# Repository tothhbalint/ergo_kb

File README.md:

## Bevezetés

##### Az ergonomikus billentyűzetek világában sok „normál” billentyűzetek ismeretében

##### furcsának tűnő megoldás van. Általában egy billentyűzeten a gombok nem egy

##### oszlopban, hanem egy kis eltolással találhatóak meg, viszont ha a billentyűket egymás

##### alá helyezzük sokkal rövidebb úton érhetőek el a gombok, ezzel csökken az újnak a

##### fáradása. Hasonlóan érdekes megoldás a billentyűzet „kettőbe vágása”, ez is a

##### kényelmet segíti, a természetes csuklópozíció megtartásával. A feladat egy ilyen

##### billentyűzet megtervezése.

##### A tervezés első fázisa a kiosztás megtervezése. Minél kevesebb gombunk van annál

##### kényelmesebb lesz gépelni, viszont időbe telhet a kiosztás megszokása. Ebben a

##### projektben egy 36 gombos kiosztás lett megvalósítva, ami pont arra elég, hogy az angol

##### ABC betűi elférjenek rajta és a végén maradjon még 1-2 gomb. Jogosan felmerülhet,

##### hogy hogyan érjük el a többi karaktert, például a számokat? Erre rétegeket

##### használhatunk, amiket erre dedikált gombokkal érhetünk el, ezek lenyomásval a

##### billentyű másik karaktert jelez a cél eszközön, hasonlóan mintha egy módosító gombot

##### használnánk. Felmerülhet még az is, hogy a módosító gombokat hogyan érjük el.

##### Többféle megoldás létezik, a legegyszerűbb talán a gombok lenyomásának idejét

##### figyelni, és a hosszan lenyomott gombokat egy adott pozícióban módosító gombként

##### kezelni.

## PCB Tervezés

### Alkatrészek

##### Fontos meghatározni az alkatrészeket mielőtt nekiállunk a PCB tervezésének, hogy

##### konkrét footprinteket (az alkatrészek lábainak az elhelyezkedése a modellben) tudjunk

##### használni. A legfontosabb alkatrészek a billentyűkapcsolók, hogy regisztrálni tudjuk a

##### billentyűlenyomásokat, a mikrokontroller, ami feldolgozza az alkatrészekből érkező

##### jeleket. Kevésbé fontos alkatrészek az enkóderek és a kijelzők.

##### Mikrokontroller választásnál két fontos szempontom volt, legyen elég GPIO lába, legyen

##### Bluetooth támogatása. Végül az nrf5284 0 - re esett a választás, ami megfelelt ezeknek a

##### követelményeknek.

##### Billentyű kapcsolókat kétféle módon tudunk beszerelni az áramkörünkbe. Vagy direktbe

##### beforrasztjuk őket, vagy használunk úgynevezett „hotswap socket”eket, amik

##### egyszerűbbé teszik a billentyűk cseréit.

### Billentyűmátrix

##### Legtöbb esetben a mikrontrollerünknek kevesebb GPIOja van mint ahány gombja van a

##### billentyűzetünknek. Ez elsőre problémának tűnik, viszont van rá egy egyszerű megoldás.

##### A kapcsolókat egy mátrixba kötjük, az alábbi módon.

###### ábra 1 :Billentyűmátrix

##### Így a kontrollernek csak annyi lába kell hogy legyen, mint ahány oszlopunk és sorunk

##### van. Az oszlopokon küldünk egy aktív jelet, amit a sorokon kiolvasunk, vagy fordítva,

##### ezzel megállapíthatjuk, hogy melyik gomb lett lenyomva, mivel az zárja az áramkört.

##### Viszont így felmerül az úgynevezett „ghosting” problémája.

###### ábra 2 : Ghosting

##### Ahogy a képen is látszik a probléma, ha a képen látható három gomb le van nyomva,

##### akkor a kontroller a C3 gombot is regisztrálja, pedig az nincsen lenyomva.

##### Erre megoldás, ha diódákat rakunk az áramkörünkbe a gombok és a sorok köze, feltéve,

##### hogy az oszlopokon küldjuk a kimenete jelen és a sorokon várjuk a bemenetit. Ekkor a

##### kép szerinti C2 gombból nem folyik áram a C3 gombba, így a 3as bemeneten nem

##### figyelünk meg jelet.

### Billentyű elosztás

##### A billentyűk elosztásának megtervezéséhez egy Ergogen nevű projektet használtam, ami

##### egy magyar fejelsztő projektje. A program egy yaml fájlból generál KiCad fájlokat, de akár

##### házat is tervezhetünk vele a billentyűzetünknek. Tervezés közben megadhatjuk a

##### gombok pozícióját, egymáshoz relatívan, a perifériák elhelyezkedését és ami a

##### legfontosabb megtudjuk adni az oszlopokhoz rendelt lábakat a mikrokontrolleren.

###### ábra 3 : Ergogen kimenet

### PCB tervezés

##### Az ergogenben elkészítettek terveket importálva kapunk egy kezdetleges NYÁK tervet,

##### ahol az összeköttetéseket és a végső elhelyezéseket fejezhetjük be.

##### A tervezés közben próbáltam figyelni rá, hogy a terv forgatható legyen, tehát mindkét

##### oldala ugyanúgy működjön, ne kelljen kettő féle prototípust legyártani. Amikor kézhez

##### kaptam akkor viszont észrevettem, hogy ez nem sikerült teljesen. Az enkóder és a kijelző

##### nem működik a megforgatott oldalon, ezt egy későbbi verzióban javítani tervezem. Ez

##### megoldható úgy, hogy a hozzájuk vezető kapcsolatot nem kötjük végig, hagyunk neki

##### kettő utat amit az összeszerelésnél összekötünk ónnal.

## Firmware

##### A firmwarrel kapcsolatos elvárások elég sztenderdek, képesnek kell lennie a perifériák

##### kezelésére, a kommunikáció helyes megvalósítására. Ahhoz hogy ezek szinkron

##### tudjanak működni, valamilyen asszinkron megoldásra lenne szükség. Példának a ZMK

##### nevű billentyűzet firmwaret használtam, ami ezt a problémát a Zephyr RTOS

##### használatával oldja meg.

##### A megvalósítás nyelvére a C/C++ lett volna az első logikus választás, viszont érdekelt,

##### hogy milyen más lehetőség vannak és hogyan lehet ezeket kihasználni. Egy ideje már ki

##### akartam próbálni, milyen Rustban beágyazott fejleszteni, a biztonsági funkciói miatt, így

##### gondoltam a projekt keretein belül megismerkedek vele.

### Rust

##### A Rust egy modern programozási nyelv, ami egyre nagyobb teret kezd hódítani magának,

##### egyre több cég, köztük a Google is kezdi preferálni C++ helyett, a biztonsági funkciói és a

##### fejlesztés ideje miatt, ami elméletben töredéke az eddig használt nyelveknek.

#### Borrow Checker és előnyei

##### A legtöbb memóriabiztos nyelv Garbage Collector segítségével oldja meg a memória

##### címek kezelését, viszont a Rust egy új megközelítést alkalmaz. Ezt Borrow Checkernek

##### nevezik, ami futás idő helyett már fordítás közben szigorú szabályokat ad meg a

##### fejlesztőnek, a kóddal kapcsolatban. A fordítás ennek következtében lassabb lesz

##### viszont a kész programunk sokkal kisebb helyet foglal, és gyorsabban is lefut, mintha

##### futás időben kezelnénk a memória hibákat.

###### ábra 5 : PCB render ábra 4 : Összeszerelt billentyűzet

##### Három fő koncepcióra bontható a működése

- Tulajdonlás

##### Minden objektumnak egyszerre csak egy tulajdonosa lehet, mint az alábbi példában

##### is látszik miután s2 átveszi a tulajdont s1 felett azután nem érhetjük el az

##### objektumot s1-en keresztül.

1. fn main() {
2. let s1 = String::from("Hello");
3. let s2 = s1; // s1 tulajdonjoga átkerül s2-höz, s1 többé nem érvényes
4.
5. // println!("{}", s1); // Ez a sor hibaüzenetet eredményezne, mert s1 már nem érvényes
6. println!("{}", s2); // s2 érvényes és használható
7. }
    - Kölcsönzés

##### Minden objektum kölcsönözhető, viszont egyszerre csak egy helyen, ha azt meg akarjuk

##### változtatni, mutábilisan (írható) akarjuk átadni. Viszont ha immutábilisan (csak

##### olvasható) akarjuk átadni, akkor több helyen is kölcsönözhetjük.

1. // This function takes ownership of a box and destroys it
2. fn eat_box_i32(boxed_i32: Box<i32>) {
3. println!("Destroying box that contains {}", boxed_i32);
4. }
5.
6. // This function borrows an i
7. fn borrow_i32(borrowed_i32: &i32) {
8. println!("This int is: {}", borrowed_i32);
9. }
10.
11. fn main() {
12. // Create a boxed i32 in the heap, and a i32 on the stack
15. let boxed_i32 : i32 = Box::new( 5 );
16. let stacked_i32 : i32 = 6 ;
17.
18. // Borrow the contents of the box. Ownership is not taken,
19. // so the contents can be borrowed again.
20. borrow_i32(&boxed_i32);
21. borrow_i32(&stacked_i32);
22.
23. {
24. // Take a reference to the data contained inside the box
25. let _ref_to_i32: &i32 = &boxed_i32;
26.
27. // Error!
28. // Can't destroy `boxed_i32` while the inner value is borrowed later in scope.
29. eat_box_i32(boxed_i32);
31.
32. // Attempt to borrow `_ref_to_i32` after inner value is destroyed
33. borrow_i32(_ref_to_i32);
34. // `_ref_to_i32` goes out of scope and is no longer borrowed.
35. }
36.
37. // `boxed_i32` can now give up ownership to `eat_box_32` and be destroyed
38. eat_box_i32(boxed_i32);
39. }
40.

- Élettartam

##### Az élettartamok számon tartják a referenciák érvényességét, így ellenőrzi, hogy

##### mindig érvényesek maradjanak. Erre lehet bevezetni paramétereket is, amikkel

##### tudjuk jelezni, hogy egy-egy referenciának meddig kell életben maradnia. Erre itt egy

##### példa.

1. fn longest<'a>(x: &'a str, y: &'a str) -> &'a str { // az ‘a paraméter megadja, hogy a
2. if x.len() > y.len() { // függvény által visszaadott referencia
3. x // élettartama megegyezik a
4. } else { // paraméterekével
5. y
6. }
7. }

##### Ezekkel a megoldásokkal a nyelv eléri, hogy majdnem teljesen kizárja a memória

##### szivárgásos hibákat, a null referenciákat és az adatverseny problémákat.

#### Beágyazott fejlesztés

##### A nyelv előbb említett funkció ideálissá teszik beágyazott alkalmazásra, viszont van egy

##### nagy hátránya. Lévén, hogy modern, friss nyelv még nincs akkora támogatása, mint

##### jobban elterjedt nyelveknek. Ez megnehezítheti nagyban az életünkent, viszont

##### szerencsére egyre többen használják és támogatjak, így egyre több crate (így hivják a

##### libraryket) és eszköz van amik segítenek a fejlesztés folyamataiban. A legfontosabb ilyen

##### eszköz a nyelv fő fordító-mindenes eszköze a cargo. Ez kezeli az összes

##### dependenciánkat, a fordítás közben tippeket ad a hibák feloldására, és ami a

##### legfontosabb külső debugger segítségével képes írni a kontrollerünkre, debugolni és

##### logolni a futást.

##### Az előbb említett cratek közül kettőt említenék meg amik fontos szerepet játszanak a

##### projekt megvalósításában.

- **Embassy**

##### Az embassy projekt célja, hogy platformfüggetlen aszinkron kódot tudjunk írni

##### beágyazott rendszerekre, megtartva a Rust modelljének az előnyeit. Az aszinkron

##### működés egy ilyen projektben nagyon fontos, mivel egyszerre több I/O műveletet

##### végzünk akár, miközben a perifériákat is le kell kezelnünk. A platformfüggetlenség

##### nem olyan fontos a projektben, viszont a modularítását elősegíti, későbbiekben

##### nem kell újraírni a kódbázist, ha más kontrollerre szeretnénk váltani.

- **probe-rs**

##### Ez egy eszköz/könyvtár csomag rustban való beágyazott fejlesztéshez, lehetőve

##### teszi, hogy a cargon keresztül flasheljük, futtasuk a kódot a chipen. A kód

##### szempontjából lehetőséget ad a logolás egyszerű megvalósítására, külső

##### debuggereken keresztül.

### Tervezés

##### A tervezésnél fontos volt figyelembe venni a modularitást, mivel a két oldal több fajta

##### konfigurációban is tud működni, nem lenne érdemes minden konfigurációt külön

##### lefejleszteni, ha váltani szeretnénk köztuk csak a main fájlunkat kell módosítani.

#### Struktúra

##### A struktúra felosztását úgy kellett megoldani, hogy feladatkörönként elkülönüljenek az

##### elemek, hogy a párhuzamos futás közben ne kelljen köztük erőforrást megosztani.

##### A fő megvalósítandó elemek maga a billentyűzet perifériák kezelő egysége és a

##### kommunikációt kezelő egységek. Érdemes arra is figyelni, hogy ezeknek csináljunk egy

##### wrappert, hogy könnyen lehessen váltani USB és Bluetooth kommunikáció között.

### Megvalósítás

#### Billentyűzet funkciók

##### A billentyűzet struktúrája:

1. pub struct Keyboard<
2. In : InputPin,
3. Out : OutputPin
4. > {
5. input_pins: [In ; 4 ],
6. output_pins: [Out ; 5 ],
7. key_states: [[KeyState; 4 ]; 5 ],
8. key_map: KeyMap,
9. report : KeyboardReport,
10. should_report : bool,
11. }

###### A fő osztály ami összefogja a billentyűzet funkcióit

1. pub(crate) struct KeyState {
2. pressed : bool,
3. pub changed : bool,
4. pressed_time : Option<Instant>,
5. debounce_counter : DebounceCounter,
6. last_tick : u32,
7. }

###### Egy-egy gomb állapotát kezelő osztály

##### Debounce

##### A debouncing algoritmus feladata hogy a kontakt zajt kiszürje, tehát egy billentyű

##### lenyomást tényleg egyként regisztráljon. Ennek a megvalósításra az alábbi algoritmust

##### implementeltám, amit a ZMK billentyűzet firmware is alkalmaz.

1. /* Step 1: Update the integrator based on the input signal. Note that the
2. integrator follows the input, decreasing or increasing towards the limits as
3. determined by the input state (0 or 1). */
4.
5. if (input == 0 )
6. {
7. if (integrator > 0 )
8. integrator--;
9. }
10. else if (integrator < MAXIMUM)
11. integrator++;
12.
13. /* Step 2: Update the output state based on the integrator. Note that the
14. output will only change states if the integrator has reached a limit, either
15. 0 or MAXIMUM. */
16.
17. if (integrator == 0 )
18. output = 0 ;
19. else if (integrator >= MAXIMUM)
20. {
21. output = 1 ;
22. integrator = MAXIMUM; /* defensive code if integrator got corrupted */
23. }
24.

##### Az alább pedig látható az implementációm, ahol a DebounceCounter osztály kezeli az

##### integrátorra vonatkozó szabályokat a fenti példából.

1. pub(crate) fn debounce_keys(key_state : &mut KeyState,pin_state : bool) - > bool {
2. let cur_tick = Instant::now().as_ticks() as u32;
3. let elapsed = (cur_tick - key_state.last_tick) as u16;
4. if elapsed > 0 {
5. if pin_state == key_state.pressed {
6. key_state.debounce_counter.decrement_counter(elapsed);
7. }
8. else {
9. if key_state.debounce_counter. 0 < DEBOUNCE_THRESHOLD * 10 {
10. key_state.debounce_counter.increment_counter(elapsed);
11. } else {
12. key_state.last_tick = cur_tick;
13. key_state.debounce_counter.reset();
14. return true
15. }
16. }
17. }
18. false
19. }
20.

##### Matrix Polling

##### A gombok lekezeléséhez így már megvan minden eszközünk, már csak meg kell

##### valósítani azt. Itt egyszerűen csak egyenként jelet adunk a kimeneteknek, ebben az

##### esetben az oszlopoknak, aztán végig nézzük a sorokat, hogy van e rajtuk jel és

##### elvégezzük a debouncingot, hogy kiszűrjuk a hamis jeleket.

1. async fn scan(&mut self) {
2. for (out_idx, out_pin) in self.output_pins.iter_mut().enumerate() {
3. out_pin.set_high().ok();
4. Timer::after_micros( 1 ).await;
5. for (in_idx, in_pin) in self.input_pins.iter_mut().enumerate() {
6. let current = in_pin.is_high().ok().unwrap_or_default();
7. let changed = debounce_keys(&mut self.key_states[out_idx][in_idx], current);
8.
9. if changed {
10. self.key_states[out_idx][in_idx].toggle_key();
11. }
12.
13. self.key_states[out_idx][in_idx].changed = changed;
14. }
15. out_pin.set_low().ok();
16. }
17. }
18.

##### Végül az üzenet elküldése előtt ki olvassuk a billentyűk állapotát és megalkotjuk a report

##### tömbünket, amit ha nem üres ki küldhetünk a választott I/O eszközön keresztül.

#### Kommunikáció

##### USB

##### Az USBn történő kommunikációnál az első feladatunk a kapcsolat felépítése a

##### céleszközzel, egy HID (Human Interface Device) descriptor generálásával jeleznünk kell

##### felé az eszközünk típusát, a tőle elvárt kommunikációt. Ezután fenn kell tartanunk a

##### kapcsolatot és szabadon tudunk a megadott paraméterekkel üzeneteket küldeni.

##### Bluetooth

##### A két oldal közti kommunikáció megvalósításának az első lépése a két oldal párosítása.

##### Ezt minden indításnál meg kell tennünk, ha nem használunk belső tárhelyet.

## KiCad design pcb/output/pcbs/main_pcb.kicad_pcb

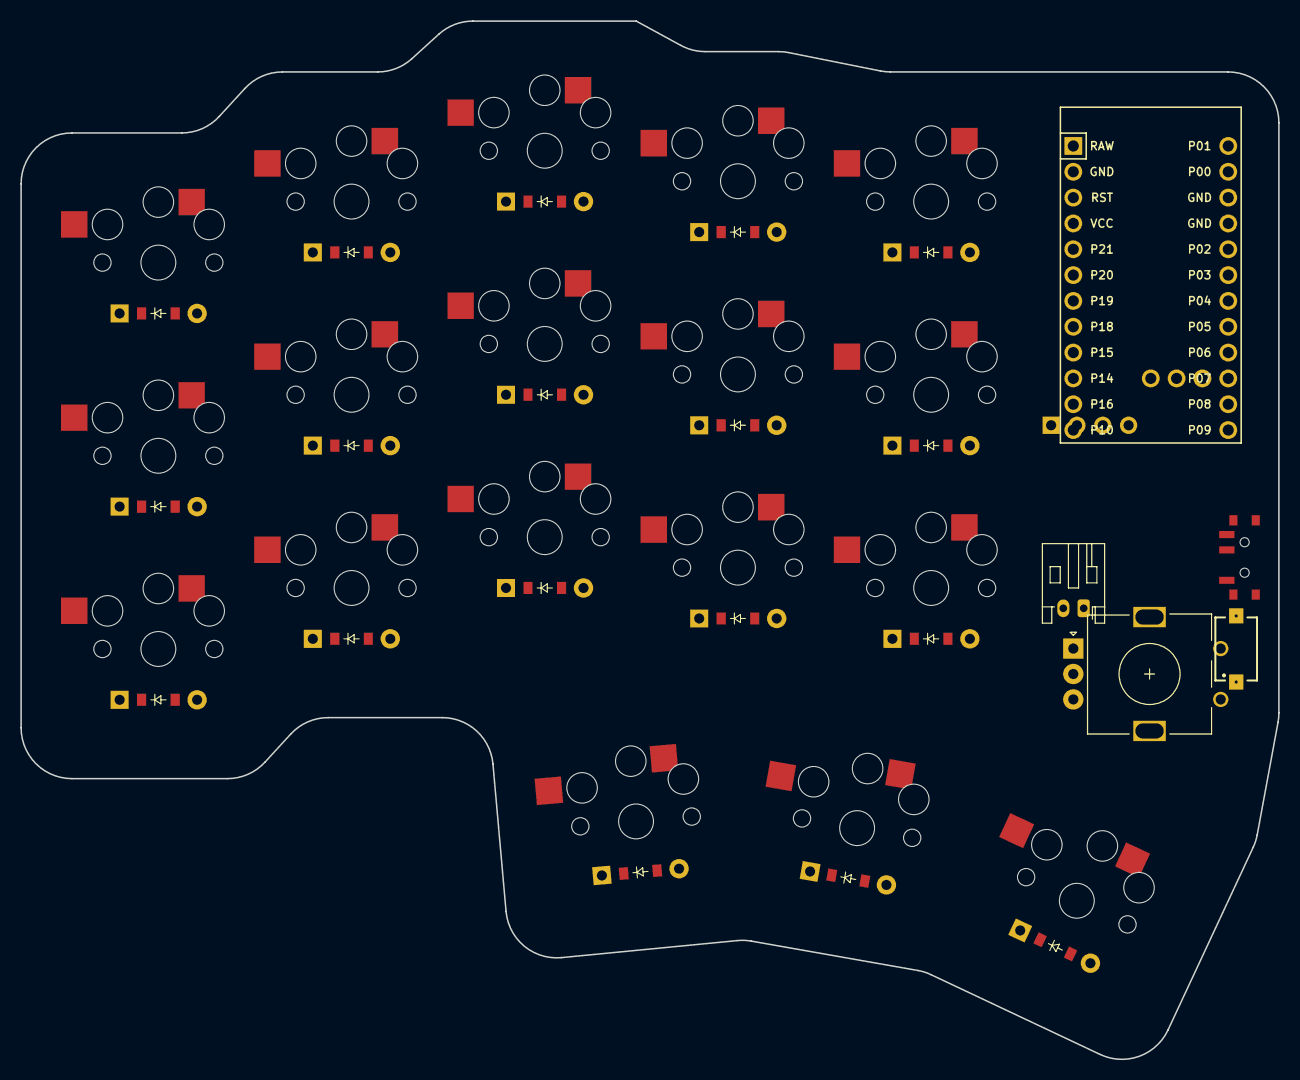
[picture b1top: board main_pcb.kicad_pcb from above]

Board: 2 copper layers, 123.7 x 102.1 mm, 42 parts (0 on the bottom side), 37 nets, no tracks yet.

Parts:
D1, D2, D3, D4, D5, D6, D7, D8, D9, D10, D11, D12, D13, D14, D15, D16, D17, D18: ComboDiode
MCU1: ProMicro
OLED1: OLED; OLED_headers
ROT1: rotary_encoder
S1, S2, S3, S4, S5, S6, S7, S8, S9, S10, S11, S12, S13, S14, S15, S16, S17, S18: PG1350
S19: 434121025816
T1: SW_SPDT_PCM12
_1: JST_PH_S2B-PH-K_1x02_P2.00mm_Horizontal

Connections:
GND: MCU1.2, MCU1.15, MCU1.16, OLED1.1, ROT1.2, ROT1.C, S19.2, _1.2
P2: MCU1.17, OLED1.4
P3: MCU1.18, OLED1.3
P5: MCU1.20, S13.1, S14.1, S15.1, S18.1
P6: MCU1.21, S10.1, S11.1, S12.1, S17.1
P7: MCU1.22, S7.1, S8.1, S9.1, S16.1
P8: MCU1.23, S4.1, S5.1, S6.1
P9: MCU1.24, S1.1, S2.1, S3.1
P14: MCU1.10, ROT1.B
P15: MCU1.9, ROT1.A
P16: MCU1.11, ROT1.1
P18: D16.1, D17.1, D18.1, MCU1.8
P19: D1.1, D4.1, D7.1, D10.1, D13.1, MCU1.7
P20: D2.1, D5.1, D8.1, D11.1, D14.1, MCU1.6
P21: D3.1, D6.1, D9.1, D12.1, D15.1, MCU1.5
RAW: MCU1.1, T1.2
RST: MCU1.3, S19.1
VCC: MCU1.4, OLED1.2
index_bottom: D10.2, S10.2
index_home: D11.2, S11.2
index_top: D12.2, S12.2
inner_bottom: D13.2, S13.2
inner_home: D14.2, S14.2
inner_top: D15.2, S15.2
layer_cluster: D17.2, S17.2
middle_bottom: D7.2, S7.2
middle_home: D8.2, S8.2
middle_top: D9.2, S9.2
mod_cluster: D16.2, S16.2
pinky_bottom: D1.2, S1.2
pinky_home: D2.2, S2.2
pinky_top: D3.2, S3.2
pos: T1.1, _1.1
ring_bottom: D4.2, S4.2
ring_home: D5.2, S5.2
ring_top: D6.2, S6.2
space_cluster: D18.2, S18.2

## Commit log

2024-02-26 initial
2024-02-26 outlines done
2024-03-21 pcb ready for order
2024-03-22 test
2024-04-05 board design 1.0 done
2024-04-05 restructuring
2024-04-30 firmware init
2024-05-01 base firmware structure
2024-05-11 usb setup done?
2024-05-12 usb comms done
2024-05-12 test commit
